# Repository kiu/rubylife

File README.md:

# rubylife
Show the world your ruby affection and live the [#BadgeLife](https://twitter.com/search?q=%23badgelife)!

# What does it do?
Besides being a stylish ruby pin, it can blink a few animations :)

# What do I need?
All you need is soldering gear (iron, tin, tweezers). Everything else is in the kit.

## I don't know how to solder!
It's easier than it looks, but a bit of help to kickstart your hardware adventure doesn't hurt. Ask your colleagues or friends for help. Or seek help in a [hackerspace](https://hackaday.io/hackerspaces) near you, they will love to teach you the ropes!

## Anything I need to know before I start?
Be aware that all parts - except for the resistors - have a polarity. Their orientation on the board is important.

Checkout this [reference](https://github.com/kiu/rubylife/raw/master/media/rubylife_polarity.jpg)!

## What is in the kit?

| Amount | Item |
| ------ | ---- |
| 1 | Printed circuit board |
| 1 | Pre-programmed microcontroller |
| 8 | Red LED |
| 8 | Resistors |
| 1 | Capacitor |
| 1 | Battery Holder |
| 1 | Battery |
| 1 | Mounting pin |
| 1 | Glue dot |

A more detailed description can be found in the [Bill-Of-Materials](https://github.com/kiu/rubylife/raw/master/bom.pdf)

# I want to write my own software
Easy, but be aware that you need C skills to proceed :/

1. Setup an ATTiny development environment, e.g. [Atmel Studio](https://www.microchip.com/mplab/avr-support/atmel-studio-7)
2. Buy a hardware programmer. Make sure it supports TPI, e.g. [USBasp](https://www.fischl.de/usbasp/)
3. Hookup VCC, GND, TPIC, TPID and RES to your programmer and power it with 5 Volts
4. ???
5. Profit!

# Who created this?
[People](https://www.schoar.de/tinkering/rubylife/) from [xbAV](https://www.xbav.de) being passionate about hardware tinkering and the ruby community.

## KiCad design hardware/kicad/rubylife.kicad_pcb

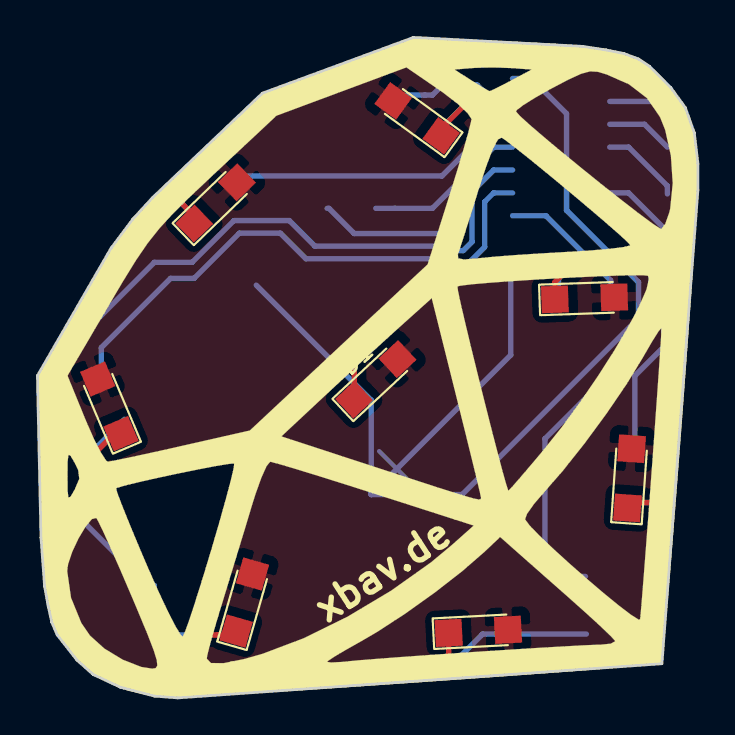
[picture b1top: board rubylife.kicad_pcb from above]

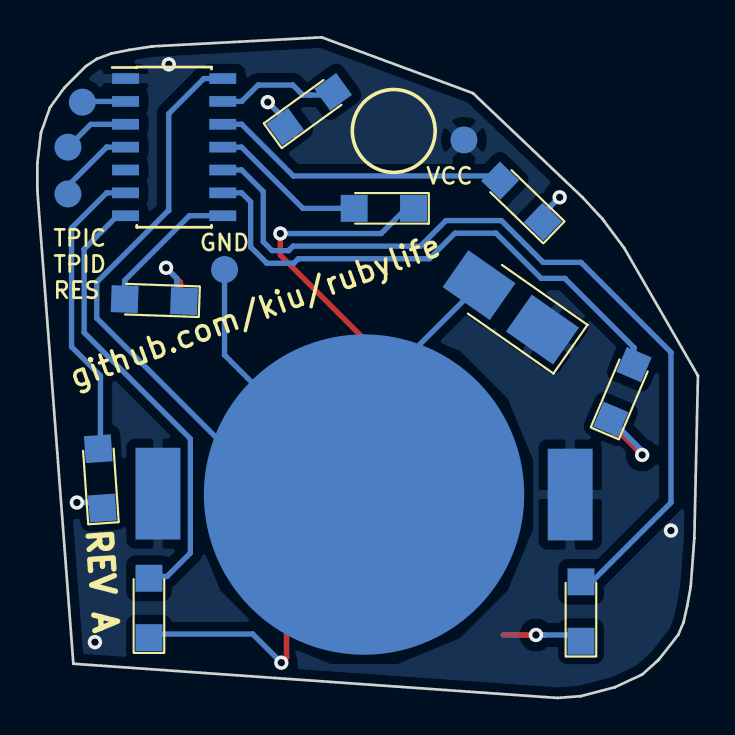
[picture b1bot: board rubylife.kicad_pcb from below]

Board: 2 copper layers, 36.7 x 36.7 mm, 24 parts (16 on the bottom side), 21 nets.

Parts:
BT1: Battery_Cell; CR2032 SMD
C1: CP; CP_Tantalum_Case-B_EIA-3528-21_Hand
D1, D2, D3, D4, D5, D6, D7, D8: LED; LED_1206
R1, R2, R3, R4, R5, R6, R7, R8: R; R_1206
TP1, TP2, TP3, TP4, TP5: TestPoint; Measurement_Point_Round-SMD-Pad_Small
U1: ATtiny20-SSU; SOIC-14_3.9x8.7mm_Pitch1.27mm

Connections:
GND: BT1.2, C1.2, TP5.1, U1.14
unnamed: D1.1, R1.1
unnamed: D2.1, R2.1
unnamed: D3.1, R3.1
unnamed: D4.1, R4.1
unnamed: D5.1, R5.1
unnamed: D6.1, R6.1
unnamed: D7.1, R7.1
unnamed: D8.1, R8.1
unnamed: R1.2, U1.11
unnamed: R2.2, U1.9
unnamed: R3.2, U1.13
unnamed: R4.2, U1.10
unnamed: R5.2, U1.8
unnamed: R6.2, U1.12
unnamed: R7.2, U1.7
unnamed: R8.2, U1.6
RESET: TP3.1, U1.4
TPIC: TP2.1, U1.2
TPID: TP1.1, U1.3
VCC: BT1.1, C1.1, D1.2, D2.2, D3.2, D4.2, D5.2, D6.2, D7.2, D8.2, TP4.1, U1.1

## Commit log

2018-12-01 hello world
